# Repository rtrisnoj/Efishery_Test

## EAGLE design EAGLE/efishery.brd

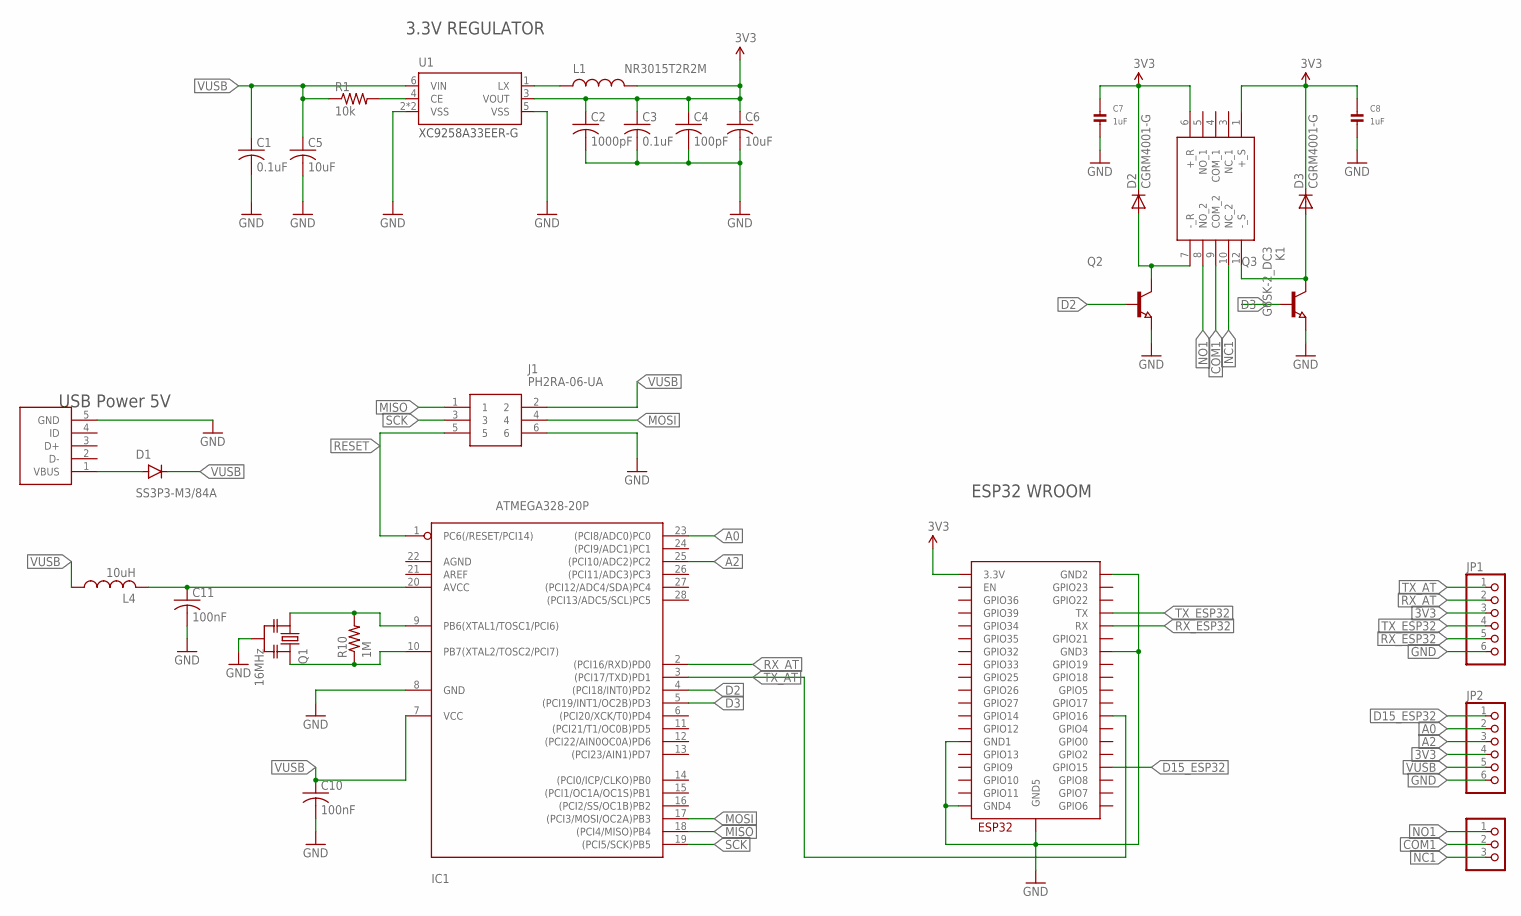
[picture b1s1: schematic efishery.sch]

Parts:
C1, C3: 0.1uF; C0402
C2: 1000pF; C0402
C4: 100pF; C0402
C5, C6: 10uF; C0603
C7, C8: 1uF; _0805
C10, C11: 100nF; 0603
D1: SS3P3-M3/84A; DIODE-DO-220AA(SMP)
D2, D3: CGRM4001-G; SOD-123_MINI-SMA
IC1: ATMEGA328-20P; DIL28-3
J1: PH2RA-06-UA; HDRRA6W64P254_2X3_762X250X500P
JP1, JP2: PINHD-1X6; 1X06
JP3: PINHD-1X3; 1X03
K1: G6SK-2_DC3; G6SK2DC3
L1: NR3015T2R2M; INDUCTOR-NR3015
L4: 10uH; L2012C
Q1: 16MHz; RESONATOR_MURATA3
Q2, Q3: NPN-TRANSISTOR_SOT23; SOT23
R1: 10k; R0402
R10: 1M; 0603
U1: XC9258A33EER-G; USP-6C
U$3: USB-MICRO-B-SOCKET-AMPHENOL; USB-B-SMT-AMPHENOL
U$4: ESP32-WROOM

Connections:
3V3: C2.1, C3.1, C4.1, C6.1, C7.1, C8.1, D2.C, D3.C, JP1.3, JP2.4, K1.1 (+_S), K1.6 (+_R), L1.2, U1.3 (VOUT), U$4.3V3 (3.3V)
A0: IC1.23 ((PCI8/ADC0)PC0), JP2.2
A2: IC1.25 ((PCI10/ADC2)PC2), JP2.3
COM1: JP3.2, K1.9 (COM_2)
D2: IC1.4 ((PCI18/INT0)PD2), Q2.1 (B)
D3: IC1.5 ((PCI19/INT1/OC2B)PD3), Q3.1 (B)
D15_ESP32: JP2.1, U$4.IO15 (GPIO15)
GND: C1.2, C2.2, C3.2, C4.2, C5.2, C6.2, C7.2, C8.2, C10.2, C11.2, IC1.8 (GND), J1.6, JP1.6, JP2.6, Q1.2, Q2.2 (E), Q3.2 (E), U1.2 (VSS), U1.5 (VSS), U1.P$1 (VSS), U$3.5 (GND), U$4.GND1, U$4.GND2, U$4.GND3, U$4.GND4, U$4.GND5
MISO: IC1.18 ((PCI4/MISO)PB4), J1.1
MOSI: IC1.17 ((PCI3/MOSI/OC2A)PB3), J1.4
unnamed: D1.ANODE, U$3.1 (VBUS)
unnamed: R1.2, U1.4 (CE)
unnamed: D2.A, K1.7 (-_R), Q2.3 (C)
unnamed: D3.A, K1.12 (-_S), Q3.3 (C)
unnamed: L1.1, U1.1 (LX)
unnamed: IC1.9 (PB6(XTAL1/TOSC1/PCI6)), Q1.1, R10.2
unnamed: IC1.10 (PB7(XTAL2/TOSC2/PCI7)), Q1.3, R10.1
unnamed: C11.1, IC1.20 (AVCC), L4.2
NC1: JP3.3, K1.10 (NC_2)
NO1: JP3.1, K1.8 (NO_2)
RESET: IC1.1 (PC6(/RESET/PCI14)), J1.5
RX_AT: IC1.2 ((PCI16/RXD)PD0), JP1.2
RX_ESP32: JP1.5, U$4.RX
SCK: IC1.19 ((PCI5/SCK)PB5), J1.3
TX_AT: IC1.3 ((PCI17/TXD)PD1), JP1.1, U$4.IO16 (GPIO16)
TX_ESP32: JP1.4, U$4.TX
VUSB: C1.1, C5.1, C10.1, D1.CATHODE, IC1.7 (VCC), J1.2, JP2.5, L4.1, R1.1, U1.6 (VIN)

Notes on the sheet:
3.3V REGULATOR
USB Power 5V
ESP32 WROOM

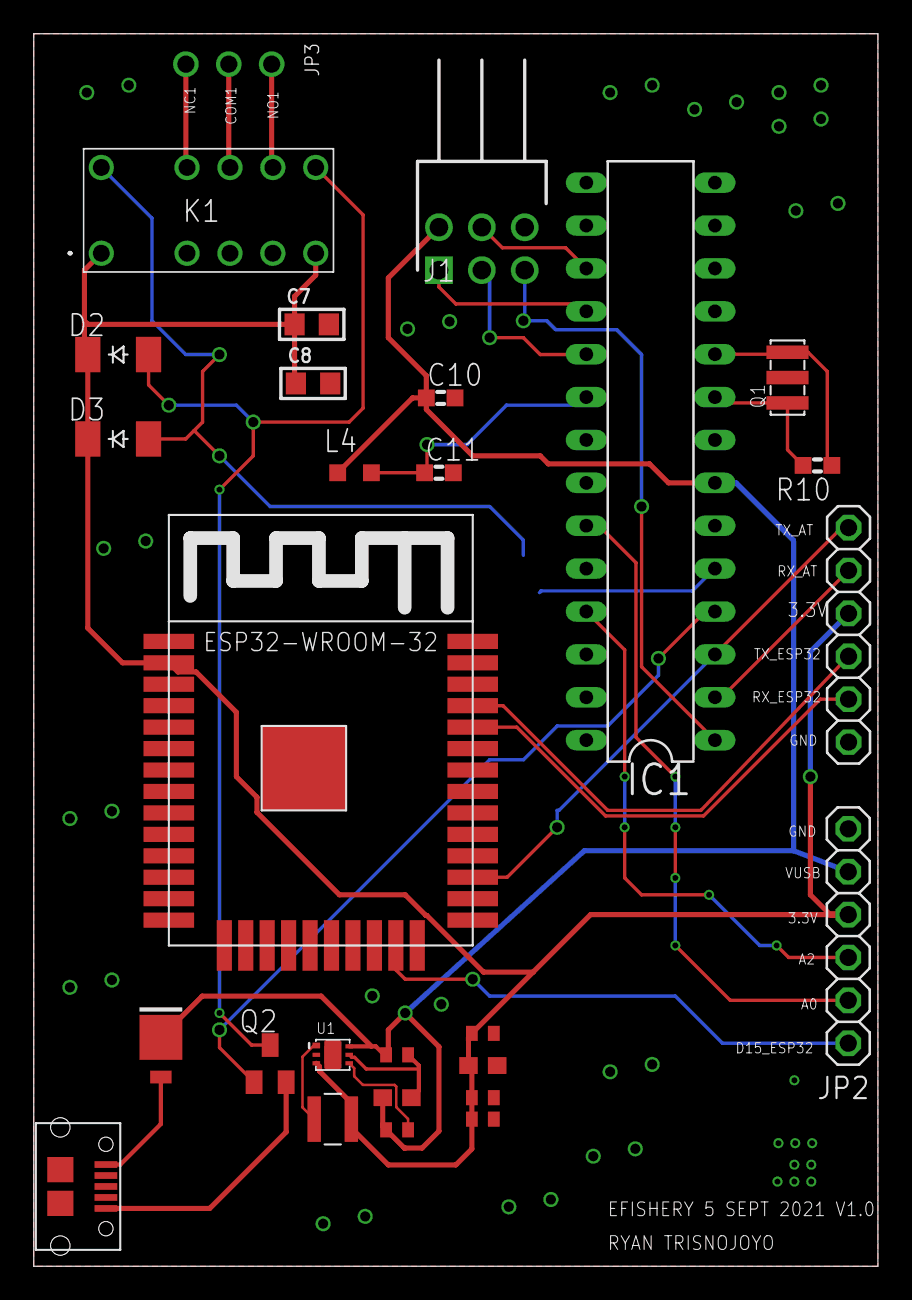
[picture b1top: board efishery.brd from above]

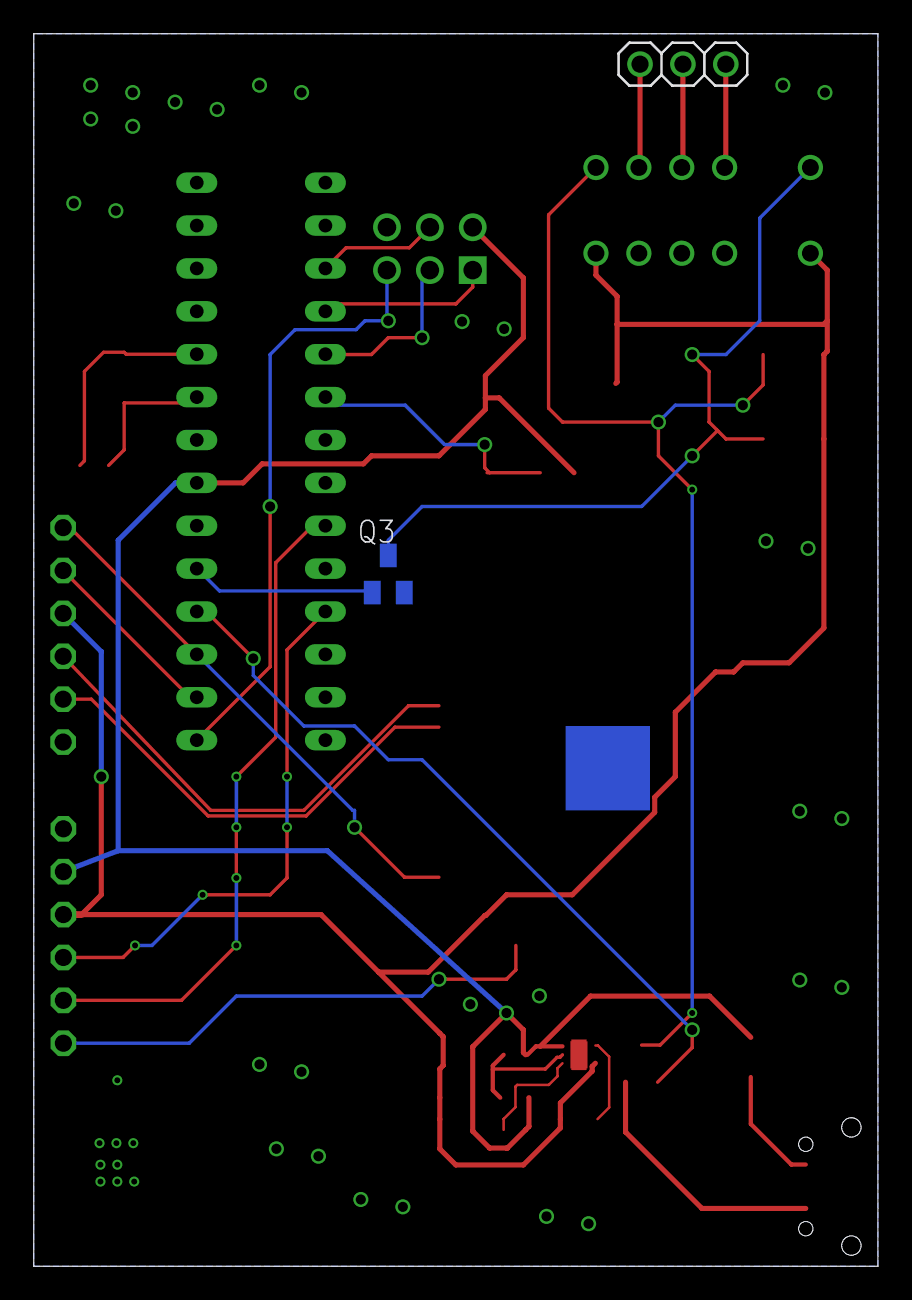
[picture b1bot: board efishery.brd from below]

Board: 2 copper layers, 50.0 x 73.0 mm, 29 parts (2 on the bottom side), 27 nets.

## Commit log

2021-09-05 final upload

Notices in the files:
parts and their libraries:
m-pad-2.1: License : GNU General Public License version 2 (see bottom)
microbuilder: This work is placed in the public domain, and may be freely used for commercial and non-commercial work with the following conditions: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
